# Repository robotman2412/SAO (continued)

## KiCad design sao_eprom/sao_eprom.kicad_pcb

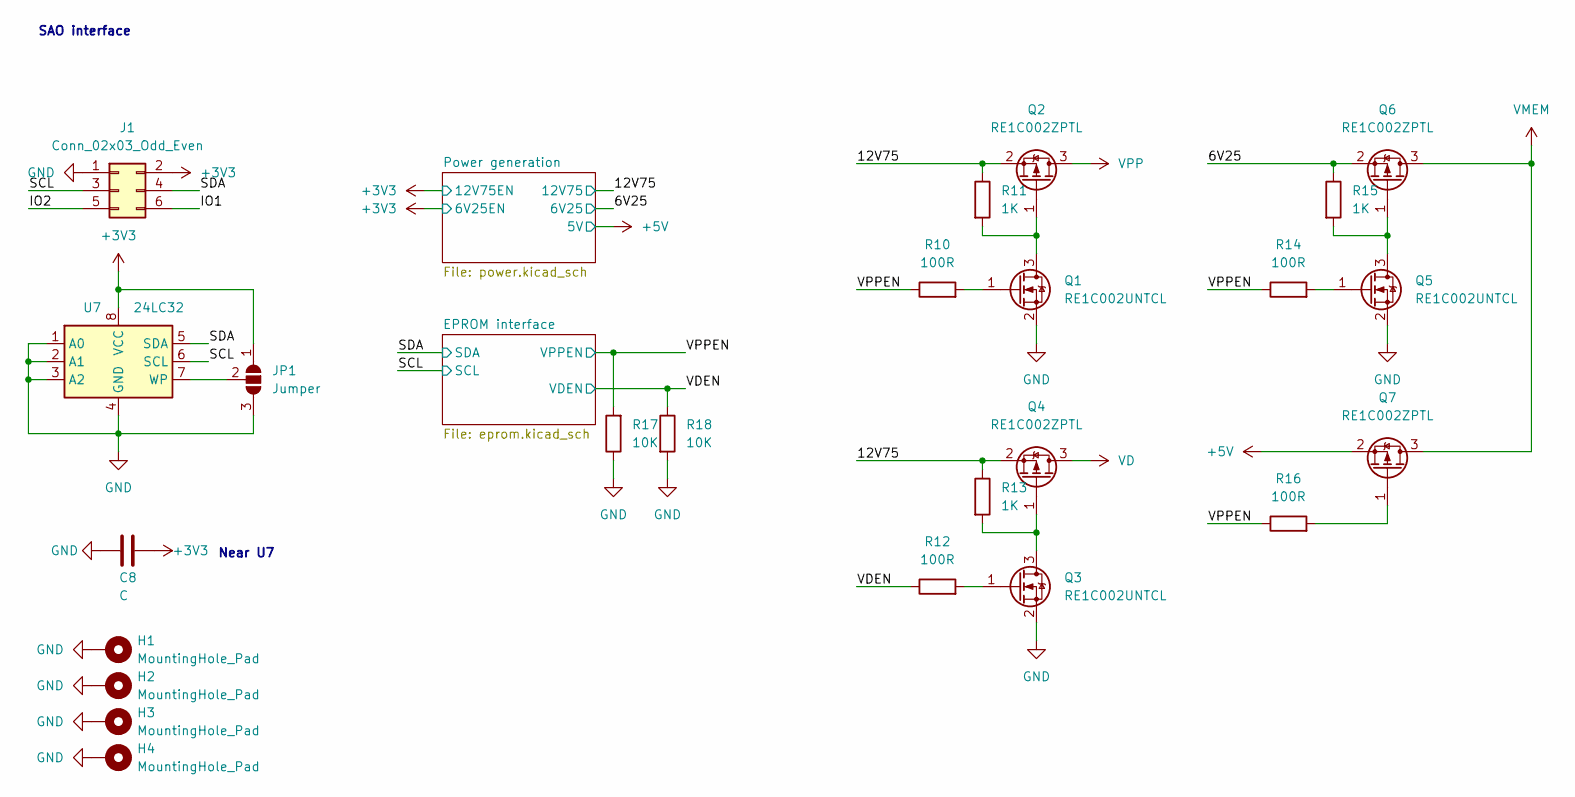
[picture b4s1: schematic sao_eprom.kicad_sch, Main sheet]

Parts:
C8: C; C_Disc_D3.0mm_W1.6mm_P2.50mm
H1, H2, H3, H4: MountingHole_Pad; MountingHole_3mm_Pad_Via
J1: Conn_02x03_Odd_Even; PinHeader_2x03_P2.54mm_Vertical
JP1: Jumper; SolderJumper-3_P1.3mm_Open_RoundedPad1.0x1.5mm_NumberLabels
Q1, Q3, Q5: RE1C002UNTCL; SOT-416
Q2, Q4, Q6, Q7: RE1C002ZPTL; SOT-416
R10, R12, R14, R16: 100R; R_Axial_DIN0207_L6.3mm_D2.5mm_P7.62mm_Horizontal
R11, R13, R15: 1K; R_Axial_DIN0207_L6.3mm_D2.5mm_P7.62mm_Horizontal
R17, R18: 10K; R_Axial_DIN0207_L6.3mm_D2.5mm_P7.62mm_Horizontal
U7: 24LC32; SOIC-8_3.9x4.9mm_P1.27mm

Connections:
+3V3: C8.1, J1.2, JP1.1 (A), U7.8 (VCC); also elsewhere on the board
+5V: Q7.2 (S); also elsewhere on the board
/6V25: Q6.2 (S), R15.1; also elsewhere on the board
/12V75: Q2.2 (S), Q4.2 (S), R11.1, R13.1; also elsewhere on the board
/IO1: J1.6
/IO2: J1.5
/SCL: J1.3, U7.6 (SCL); also elsewhere on the board
/SDA: J1.4, U7.5 (SDA); also elsewhere on the board
/VDEN: R12.1, R18.1; also elsewhere on the board
/VPPEN: R10.1, R14.1, R16.1, R17.2; also elsewhere on the board
GND: C8.2, H1.1, H2.1, H3.1, H4.1, J1.1, JP1.3 (B), Q1.2 (S), Q3.2 (S), Q5.2 (S), R17.1, R18.2, U7.1 (A0), U7.2 (A1), U7.3 (A2), U7.4 (GND); also elsewhere on the board
unnamed: JP1.2 (C), U7.7 (WP)
unnamed: Q1.1 (G), R10.2
unnamed: Q1.3 (D), Q2.1 (G), R11.2
unnamed: Q3.1 (G), R12.2
unnamed: Q3.3 (D), Q4.1 (G), R13.2
unnamed: Q5.1 (G), R14.2
unnamed: Q5.3 (D), Q6.1 (G), R15.2
unnamed: Q7.1 (G), R16.2
VD: Q4.3 (D); also elsewhere on the board
VMEM: Q6.3 (D), Q7.3 (D); also elsewhere on the board
VPP: Q2.3 (D); also elsewhere on the board

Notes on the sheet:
Near U7
SAO interface

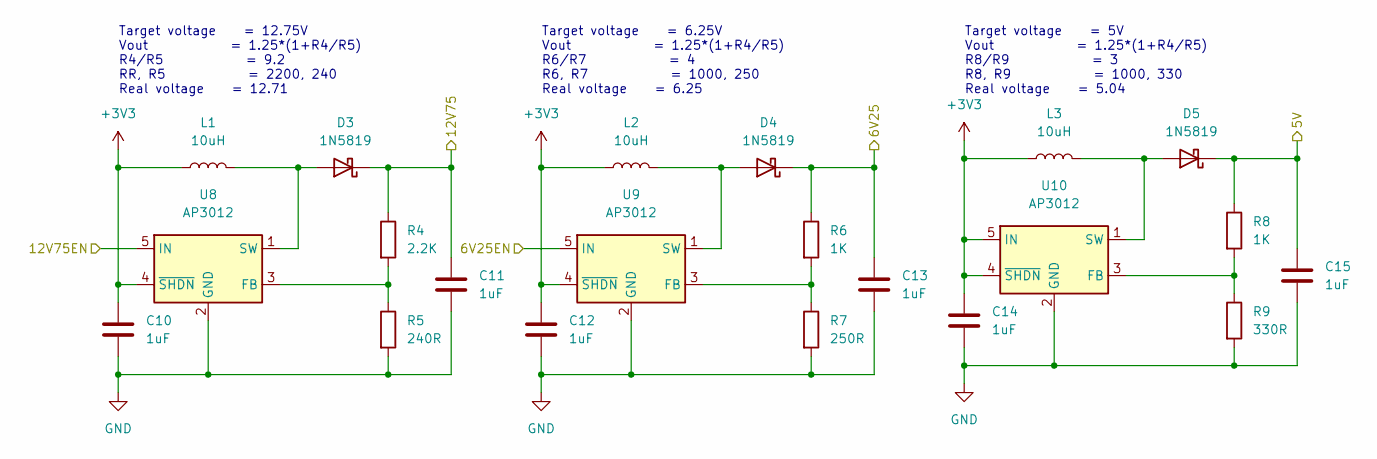
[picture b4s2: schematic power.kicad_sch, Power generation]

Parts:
C10, C11, C12, C13, C14, C15: 1uF; C_Disc_D3.0mm_W1.6mm_P2.50mm
D3, D4, D5: 1N5819; D_DO-41_SOD81_P10.16mm_Horizontal
L1, L2, L3: 10uH; L_0805_2012Metric
R4: 2.2K; R_Axial_DIN0207_L6.3mm_D2.5mm_P7.62mm_Horizontal
R5: 240R; R_Axial_DIN0207_L6.3mm_D2.5mm_P7.62mm_Horizontal
R6, R8: 1K; R_Axial_DIN0207_L6.3mm_D2.5mm_P7.62mm_Horizontal
R7: 250R; R_Axial_DIN0207_L6.3mm_D2.5mm_P7.62mm_Horizontal
R9: 330R; R_Axial_DIN0207_L6.3mm_D2.5mm_P7.62mm_Horizontal
U8, U9, U10: AP3012; SOT-23-5

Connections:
+3V3: C10.2, C12.2, C14.2, L1.1, L2.1, L3.1, U8.4 (~SHDN), U8.5 (IN), U9.4 (~SHDN), U9.5 (IN), U10.4 (~SHDN), U10.5 (IN); also elsewhere on the board
+5V: C15.2, D5.1 (K), R8.1; also elsewhere on the board
/6V25: C13.2, D4.1 (K), R6.1; also elsewhere on the board
/12V75: C11.2, D3.1 (K), R4.1; also elsewhere on the board
GND: C10.1, C11.1, C12.1, C13.1, C14.1, C15.1, R5.2, R7.2, R9.2, U8.2 (GND), U9.2 (GND), U10.2 (GND); also elsewhere on the board
unnamed: D3.2 (A), L1.2, U8.1 (SW)
unnamed: D4.2 (A), L2.2, U9.1 (SW)
unnamed: D5.2 (A), L3.2, U10.1 (SW)
unnamed: R4.2, R5.1, U8.3 (FB)
unnamed: R6.2, R7.1, U9.3 (FB)
unnamed: R8.2, R9.1, U10.3 (FB)

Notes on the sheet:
Target voltage = 12.75V Vout = 1.25*(1+R4/R5) R4/R5 = 9.2 RR, R5 = 2200, 240 Real voltage = 12.71
Target voltage = 6.25V Vout = 1.25*(1+R4/R5) R6/R7 = 4 R6, R7 = 1000, 250 Real voltage = 6.25
Target voltage = 5V Vout = 1.25*(1+R4/R5) R8/R9 = 3 R8, R9 = 1000, 330 Real voltage = 5.04

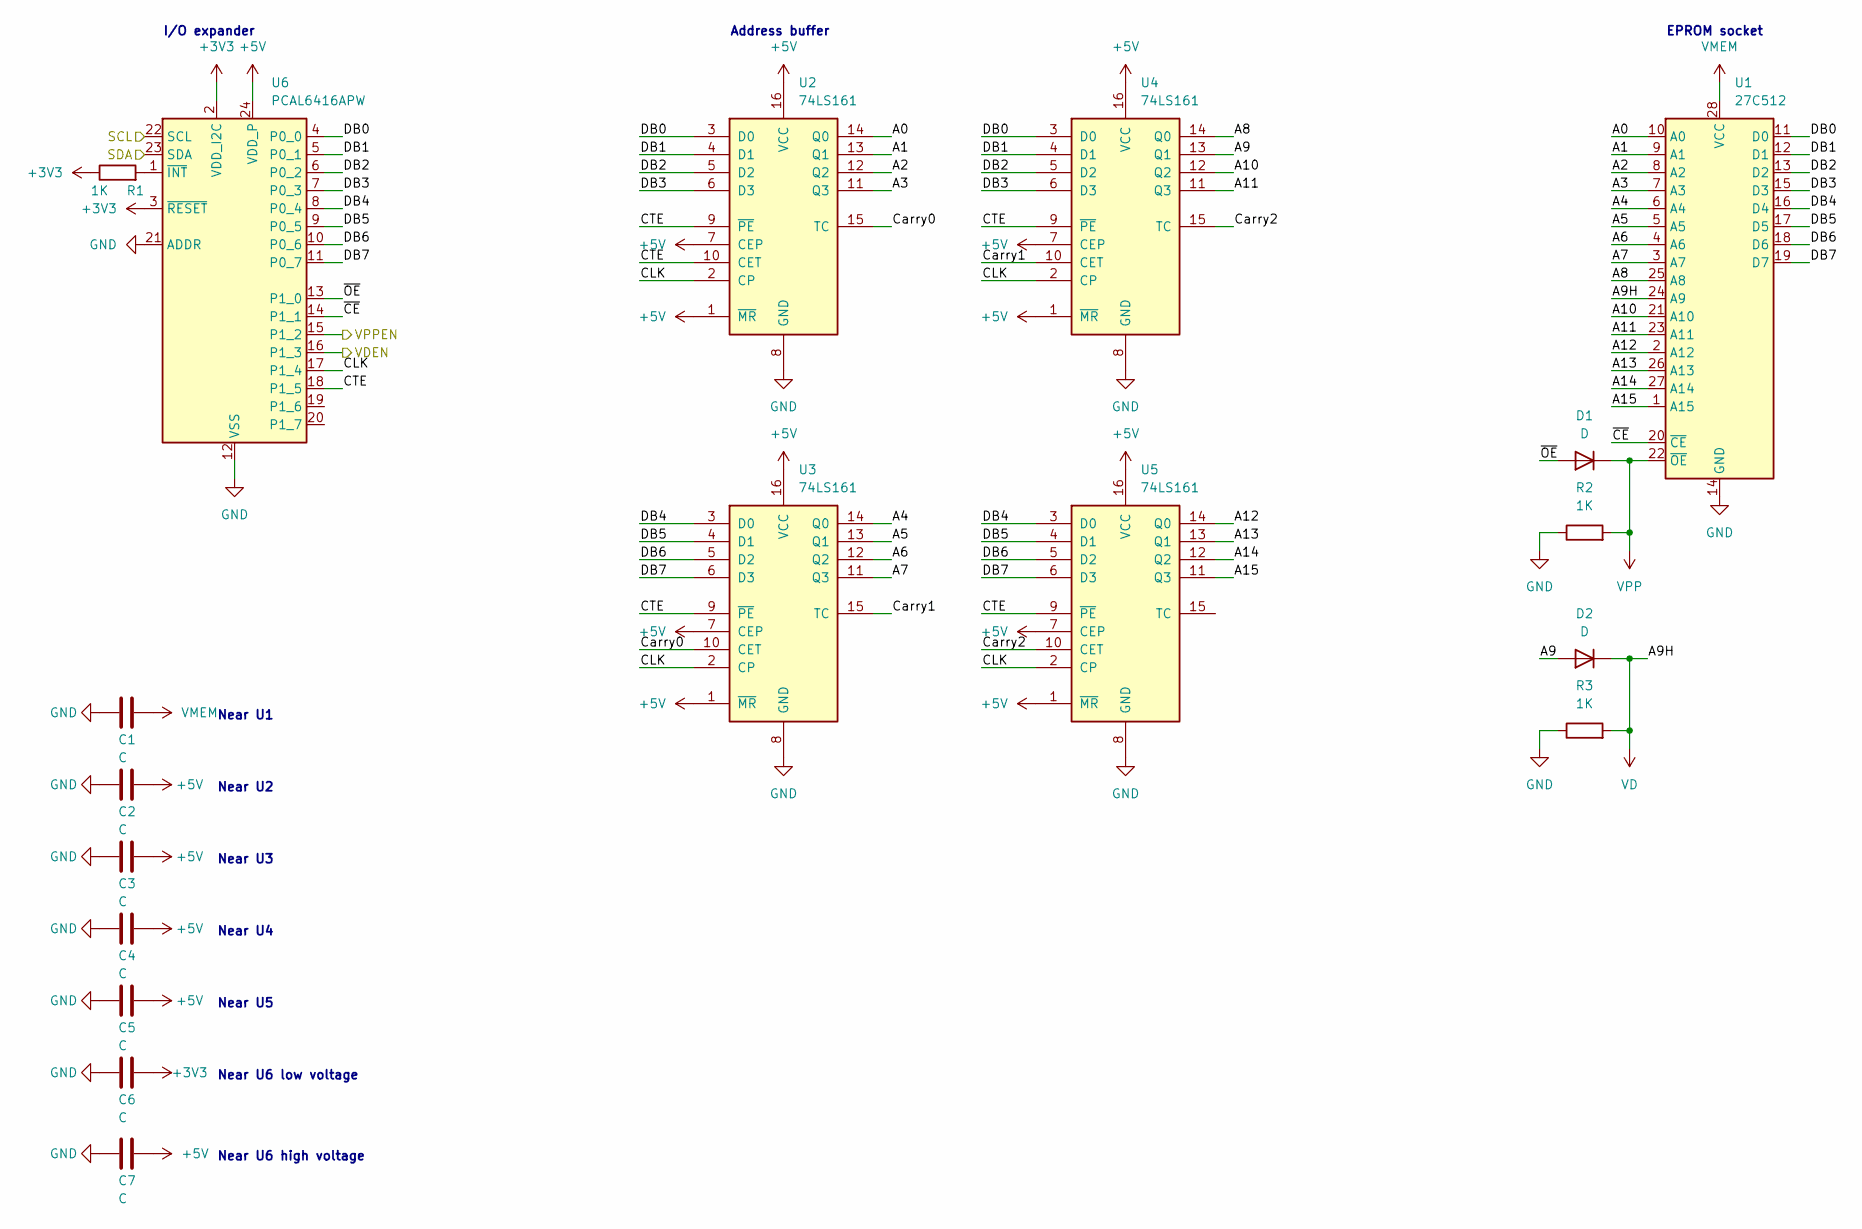
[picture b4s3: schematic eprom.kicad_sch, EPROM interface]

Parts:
C1, C2, C3, C4, C5, C6, C7: C; C_Disc_D3.0mm_W1.6mm_P2.50mm
D1, D2: D; D_DO-41_SOD81_P10.16mm_Horizontal
R1, R2, R3: 1K; R_Axial_DIN0207_L6.3mm_D2.5mm_P7.62mm_Horizontal
U1: 27C512; DIP-28_W15.24mm
U2, U3, U4, U5: 74LS161; DIP-16_W7.62mm
U6: PCAL6416APW; TSSOP-24_4.4x7.8mm_P0.65mm

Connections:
+3V3: C6.1, R1.1, U6.2 (VDD_I2C), U6.3 (~RESET); also elsewhere on the board
+5V: C2.1, C3.1, C4.1, C5.1, C7.1, U2.1 (~MR), U2.7 (CEP), U2.16 (VCC), U3.1 (~MR), U3.7 (CEP), U3.16 (VCC), U4.1 (~MR), U4.7 (CEP), U4.16 (VCC), U5.1 (~MR), U5.7 (CEP), U5.16 (VCC), U6.24 (VDD_P); also elsewhere on the board
/EPROM interface/A0: U1.10 (A0), U2.14 (Q0)
/EPROM interface/A1: U1.9 (A1), U2.13 (Q1)
/EPROM interface/A2: U1.8 (A2), U2.12 (Q2)
/EPROM interface/A3: U1.7 (A3), U2.11 (Q3)
/EPROM interface/A4: U1.6 (A4), U3.14 (Q0)
/EPROM interface/A5: U1.5 (A5), U3.13 (Q1)
/EPROM interface/A6: U1.4 (A6), U3.12 (Q2)
/EPROM interface/A7: U1.3 (A7), U3.11 (Q3)
/EPROM interface/A8: U1.25 (A8), U4.14 (Q0)
/EPROM interface/A9: D2.2 (A), U4.13 (Q1)
/EPROM interface/A10: U1.21 (A10), U4.12 (Q2)
/EPROM interface/A11: U1.23 (A11), U4.11 (Q3)
/EPROM interface/A12: U1.2 (A12), U5.14 (Q0)
/EPROM interface/A13: U1.26 (A13), U5.13 (Q1)
/EPROM interface/A14: U1.27 (A14), U5.12 (Q2)
/EPROM interface/A15: U1.1 (A15), U5.11 (Q3)
/EPROM interface/CLK: U2.2 (CP), U3.2 (CP), U4.2 (CP), U5.2 (CP), U6.17 (P1_4)
/EPROM interface/CTE: U2.9 (~PE), U2.10 (CET), U3.9 (~PE), U4.9 (~PE), U5.9 (~PE), U6.18 (P1_5)
/EPROM interface/Carry0: U2.15 (TC), U3.10 (CET)
/EPROM interface/Carry1: U3.15 (TC), U4.10 (CET)
/EPROM interface/Carry2: U4.15 (TC), U5.10 (CET)
/EPROM interface/DB0: U1.11 (D0), U2.3 (D0), U4.3 (D0), U6.4 (P0_0)
/EPROM interface/DB1: U1.12 (D1), U2.4 (D1), U4.4 (D1), U6.5 (P0_1)
/EPROM interface/DB2: U1.13 (D2), U2.5 (D2), U4.5 (D2), U6.6 (P0_2)
/EPROM interface/DB3: U1.15 (D3), U2.6 (D3), U4.6 (D3), U6.7 (P0_3)
/EPROM interface/DB4: U1.16 (D4), U3.3 (D0), U5.3 (D0), U6.8 (P0_4)
/EPROM interface/DB5: U1.17 (D5), U3.4 (D1), U5.4 (D1), U6.9 (P0_5)
/EPROM interface/DB6: U1.18 (D6), U3.5 (D2), U5.5 (D2), U6.10 (P0_6)
/EPROM interface/DB7: U1.19 (D7), U3.6 (D3), U5.6 (D3), U6.11 (P0_7)
/EPROM interface/~CE: U1.20 (~CE), U6.14 (P1_1)
/EPROM interface/~OE: D1.2 (A), U6.13 (P1_0)
/SCL: U6.22 (SCL); also elsewhere on the board
/SDA: U6.23 (SDA); also elsewhere on the board
/VDEN: U6.16 (P1_3); also elsewhere on the board
/VPPEN: U6.15 (P1_2); also elsewhere on the board
GND: C1.2, C2.2, C3.2, C4.2, C5.2, C6.2, C7.2, R2.1, R3.1, U1.14 (GND), U2.8 (GND), U3.8 (GND), U4.8 (GND), U5.8 (GND), U6.12 (VSS), U6.21 (ADDR); also elsewhere on the board
unnamed: R1.2, U6.1 (~INT)
VD: D2.1 (K), R3.2, U1.24 (A9); also elsewhere on the board
VMEM: C1.1, U1.28 (VCC); also elsewhere on the board
VPP: D1.1 (K), R2.2, U1.22 (~OE); also elsewhere on the board

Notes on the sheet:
Near U3
Near U6 high voltage
I/O expander
EPROM socket
Near U1
Near U4
Near U6 low voltage
Address buffer
Near U5
Near U2

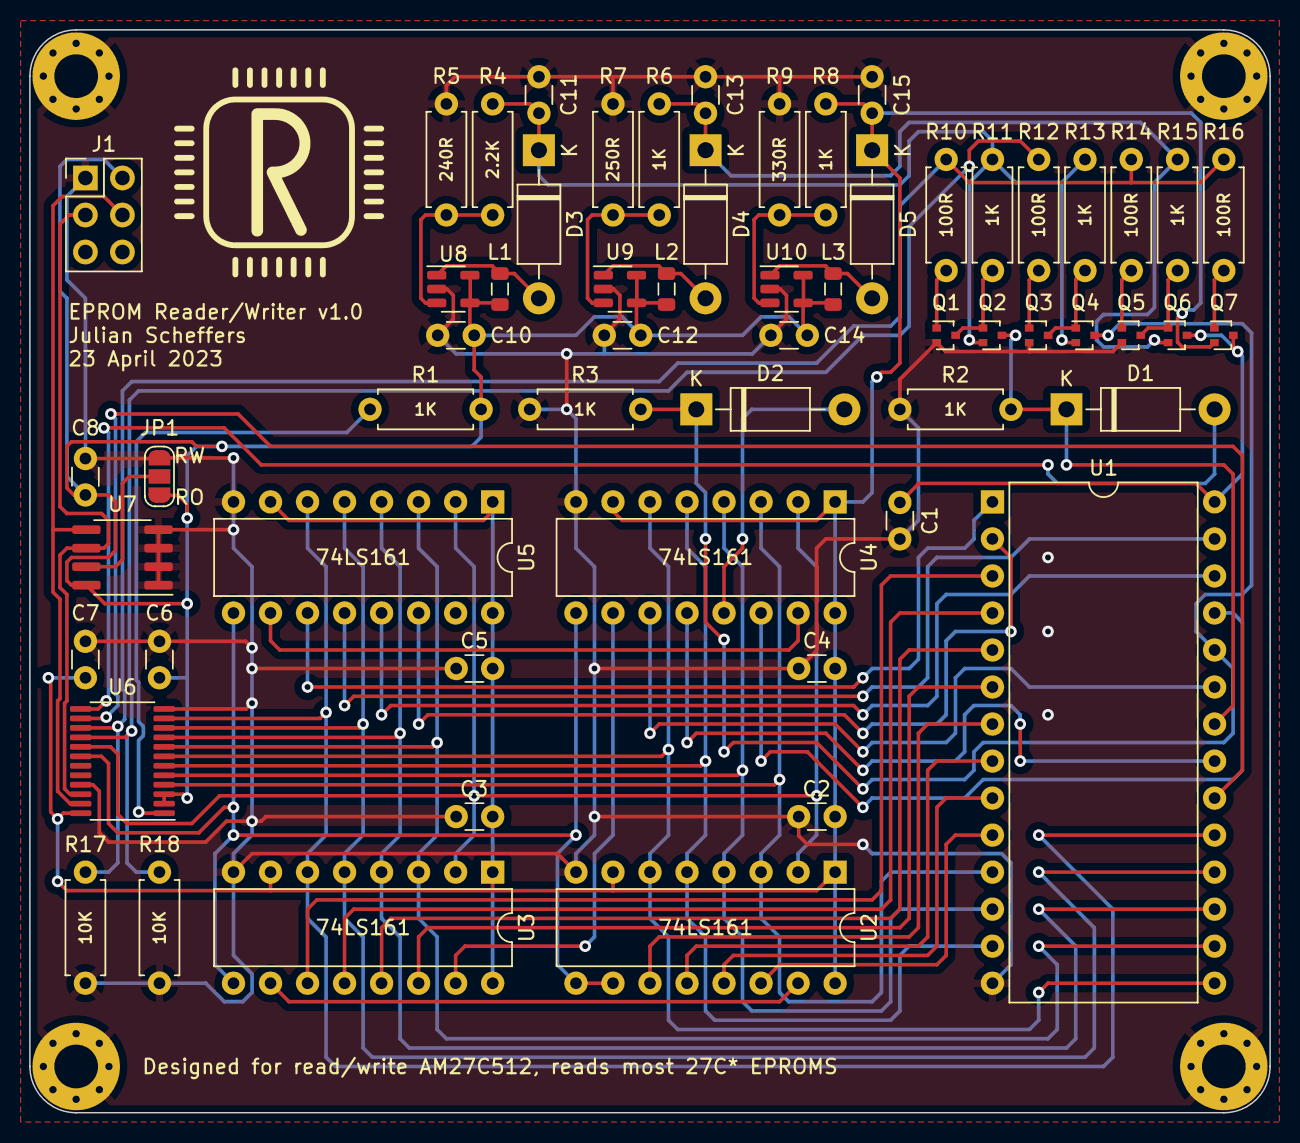
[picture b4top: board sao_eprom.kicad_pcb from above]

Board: 2 copper layers, 85.1 x 74.3 mm, 63 parts (0 on the bottom side), 58 nets.

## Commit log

2023-04-15 Initial commit.
2023-04-15 Create gitignore
2023-04-21 Does more designing ROMulator
2023-04-21 Reworks the address circuit
2023-04-23 I know how 2 power now
2023-04-23 Finish the first design revision
2023-04-23 asdafdafa
2023-04-24 Do some resistor calculations
2023-04-24 Now with calculation scripts
2023-05-08 Choose final resistor values
2023-05-09 Prepare for the ORDERING
2023-05-09 Update GITIGNORE
2023-05-09 I am making rev 2 because rev 1 is very not working
2023-06-04 More works on eprom v2
2023-06-04 the experiment
2023-06-05 Flip the CHIPS upside down to make routing easier
2023-06-05 More tricky routing.
2023-06-05 Nearly finished the design
2023-06-06 First complete PCB
2023-06-06 Create fabrication outputs.
2023-06-06 Work some feedback into the schematic.
2023-06-07 Add some blinkenlights!
2023-06-07 Change LED order so status (on top) is first.
2023-06-08 Now with QWIIC and TestPads!
2023-06-08 Label the test pads
2023-06-08 Bump date
2023-06-08 Most important commit in the history of the entire world
2023-06-09 Another keyboard
2023-06-09 Remove the old one
2023-06-10 Sketch up keyboard footprints.
2023-06-10 Keyboard addon Rev. 1
2023-06-17 Put yet another feedback in my design
2023-06-17 Phisinsh another design rephision.
2023-06-18 Candidate revision No. 1
2023-07-04 More EPROM devving
2023-07-05 Remove mounting holes from BOM
2023-07-05 Curvify the keyboard
2023-07-05 Add some lights to the keyboard addon.
2023-07-05 A barebones circular blinky SAO
2023-07-05 Generate fabrication outputs
2023-07-06 Finish the keyboard design
2023-07-06 Keyboard fabrication outputs
